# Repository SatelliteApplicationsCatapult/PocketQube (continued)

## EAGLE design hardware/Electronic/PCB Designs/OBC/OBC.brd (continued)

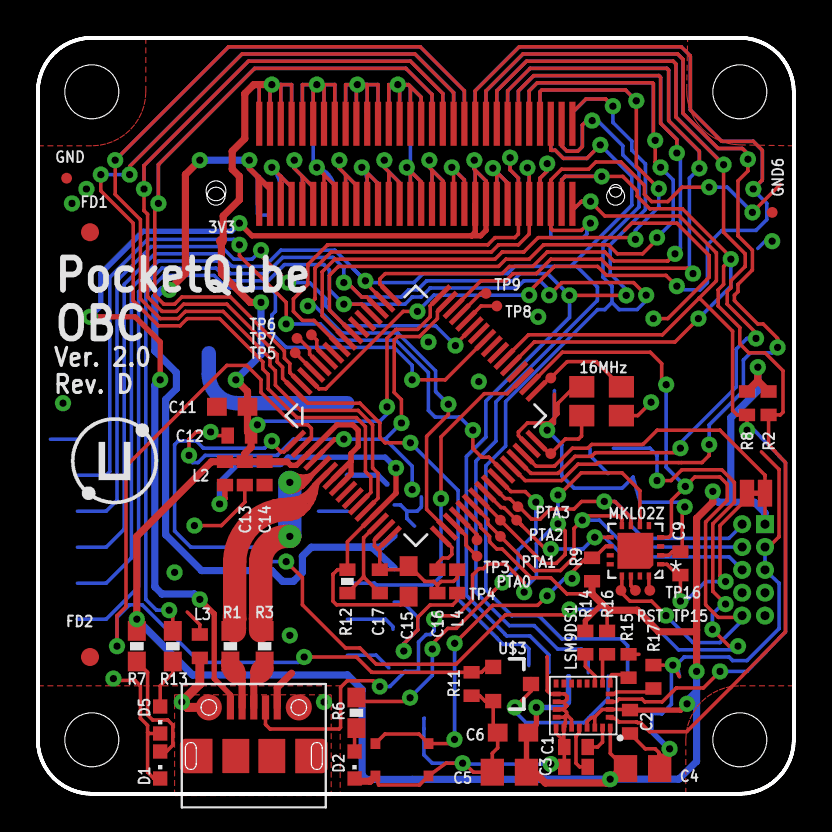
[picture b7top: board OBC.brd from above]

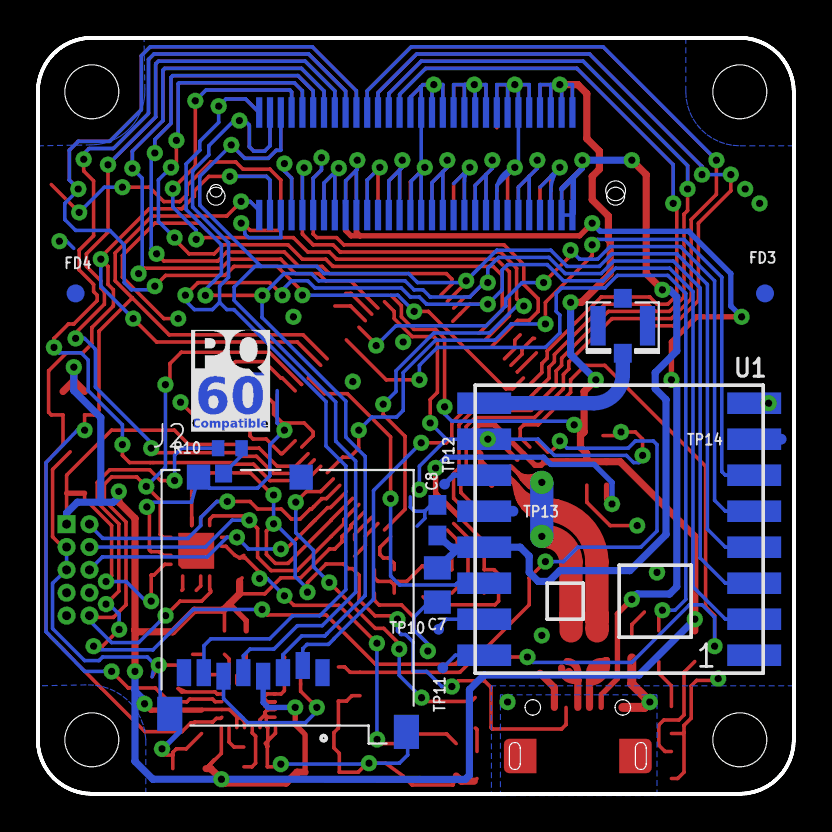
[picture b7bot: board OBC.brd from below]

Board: 2 copper layers, 42.0 x 42.0 mm, 82 parts (16 on the bottom side), 79 nets.

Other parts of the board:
U$2: PQ60_CMP
U$10: UBO_LOGO
U$13: SA_LOGO_SMALL

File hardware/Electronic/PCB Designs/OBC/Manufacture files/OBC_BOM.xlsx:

Parts | Manufacturer | Part number | Value | Qty | Package | Description | Distributor | Order code | Notes | ROHS | Temp range
3V3, GND, GND6, PTA0, PTA1, PTA2, PTA3, RST, TP1, TP2, TP3, TP4, TP5, TP6, TP7,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 |  | PTR1TP06R |  | 24 | TP06R | TEST PIN |  |  | Do not populate
C1, C2, C9, C12, C13, C14, C16, C17 |  | C-EUC0402 | 0.1uF | 8 | C0402 | CAPACITOR, European symbol |  |  | Any compatible X7R MLCC
C11, C15 |  | C-EUC0603 | 2.2uF | 2 | C0603 | CAPACITOR, European symbol |  |  | Any compatible X7R MLCC
C3 |  | C-EUC0402 | 10nF | 1 | C0402 | CAPACITOR, European symbol |  |  | Any compatible X7R MLCC
C4, C5, C7 |  | C-EUC0805 | 10uF | 3 | C0805 | CAPACITOR, European symbol |  |  | Any compatible X7R MLCC
C6, C8 |  | C-EUC0603 | 1uF | 2 | C0603 | CAPACITOR, European symbol |  |  | Any compatible X7R MLCC
D1 | Kingbright | KPT-1608EC | Red | 1 | CHIPLED_0603 | LED | Farnell | 2099221RL | Or any compatible 0603 SMD low power red LED | Yes | -40 to 85
D2 | Kingbright | KPG-1608QBC-D | Blue | 1 | CHIPLED_0603 | LED | Farnell | 1686063RL | Or any compatible 0603 SMD low power blue LED | Yes | -40 to 85
D5 | Kingbright | KPTD-1608SYCK | Yellow | 1 | CHIPLED_0603 | LED | Farnell | 2449898 | Or any compatible 0603 SMD low power yellow LED | Yes | -40 to 85
ERASE | Panasonic | EVPAF7B70 |  | 1 | EVPAF7B70 | Tactile switch | Farnell | 2425605 | Alternative suppliers available | Yes | -40 to 85
FD1, FD2, FD3, FD4 |  | FIDUCIAL |  | 4 | FIDUCIAL_1MM | For use by pick and place machines to calibrate the vision/machine, 1mm |  |  | Do not populate
J2 | Molex | 47352-1001 |  | 1 | MOLEX_47352-1001 | 1.10mm Pitch microSD Card Connector, Push-Push Type, with VSS (Supply Voltage G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 | RS Components | 720-6016P | Alternative suppliers available | Yes | -20 to 85
L2, L3, L4 | Murata | BLM15HG601SN1 |  | 3 | 402 | EMIFIL (R) Chip Ferrite Bead for GHz Noise | RS Components | 724-1289P | Alternative suppliers available | Yes | -55 to 125
LSM9DS1 | STMicroelectronics | LSM9DS1TR |  | 1 | LGA24-8X4 | LSM9DS1 3D accelerometer, gyroscope & magnetometer | Mouser | 511-LSM9DS1TR | Alternative suppliers available | Yes | -40 to 85
NDK_NX3225SA | Epson | X1E0000210117 TSX-3225 16MHZ 9PF | 16MHz | 1 | 4SMD_DFN_LCC | 16 MHz SMD crystal | Farnell | 2471850 | Must be 16 MHz, 9 pF, ≤10ppm, 3.2x2.5 crystal | Yes | -20 to 75
PQ60_HEADER | Hirose | FX8C-60P-SV6(91) |  | 1 | FX8C-060P-SV4(92) | Header | Mouser | 798-FX8C60PSV691 | Alternative suppliers available, however ensure the FX8C60PSV6 part is used, no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 | Yes
PQ60_RECEPTACLE |  | FX8C-060S-SV(92) |  | 1 | FX8C-060S-SV(92) |  |  |  | Do not populate | Yes
R1, R3 |  | RESISTOR0603-RES | 33R | 2 | 0603-RES | Resistor |  |  | Any standard chip SMD resistor, 1% tolerance or better
R12 |  | RESISTOR0402-RES | 10K | 1 | 0402-RES | Resistor |  |  | Any standard chip SMD resistor, 1% tolerance or better
R14, R15, R16, R17 |  | R-EU_R0402 | 10K | 4 | R0402 | RESISTOR, European symbol |  |  | Any standard chip SMD resistor, 1% tolerance or better
R2, R8 |  | R-EU_R0402 | 4.7K | 2 | R0402 | RESISTOR, European symbol |  |  | Any standard chip SMD resistor, 1% tolerance or better
R6, R7, R13 |  | RESISTOR0603-RES | 330R | 3 | 0603-RES | Resistor |  |  | Any standard chip SMD resistor, 1% tolerance or better
R9, R10, R11 |  | R-EU_R0402 | 22K | 3 | R0402 | RESISTOR, European symbol |  |  | Any standard chip SMD resistor, 1% tolerance or better
SJ3 |  | SJNC |  | 1 | SJNC | Solder jumper |  |  | Do not populate
U$1 | NXP | MKL02Z32VFG4SMD |  | 1 | QFN16 | Kinetis KL02 32 KB Flash |  |  | This must be pre-programmed with Teensy bootloader. We will supply this compone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
U$11 | Molex | 105017-0001 |  | 1 | USB-MICRO-TABS | Micro USB type B connector | Farnell | 2293836 | Alternative suppliers available | Yes | -30 to 85
U$3 | Nexperia | PMV40UN2R |  | 1 | SOT23-3 | N-channel trench MOSFET | Mouser | 771-PMV40UN2R | Alternative suppliers available | Yes | -55 to 150
U$4 | NXP | MK20DX256VLH7 |  | 1 | QFP50P1200X1200X160-64N | This is a footprint for the MK20dx256VHL7, the chip at the heart of the Teensy 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 | Farnell | 2133577 | Alternative suppliers available. | Yes | -40 to 105
U$9 |  | SWD_10_PIN |  | 1 | SWD_10_PIN |  |  |  | Do not populate
U.FL | Hirose | U.FL-R-SMT-1(10) |  | 1 | U.FL | SMD antenna connector- WRL-09144 | Farnell | 1688077 | Alternative suppliers available | Yes | -40 to 90
U1 | SparkFun | COM-13910 |  | 1 | RFM69HCW-XXXS2 | Wireless transceiver | Mouser | 474-COM-13910 | Alternative suppliers available but must be 433 MHz, HCW variant | Yes | -55 to 115
 |  |  |  | Partlist exported from C:/Users/Ken.Diep/repos/hardware/Electronic/PCB Designs/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

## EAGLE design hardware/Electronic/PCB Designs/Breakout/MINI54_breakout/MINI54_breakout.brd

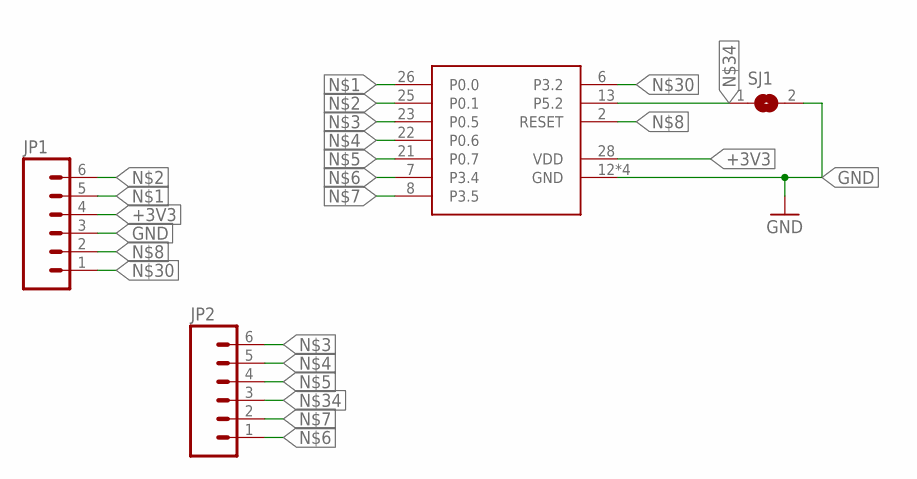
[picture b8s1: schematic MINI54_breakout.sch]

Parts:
JP1, JP2: M06LONGPADS; 1X06_LONGPADS
SJ1: SJ
U$9: MINITAN54-QFN; QFN50P500X500X100-33N

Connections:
+3V3: JP1.4, U$9.28 (VDD)
GND: JP1.3, SJ1.2, U$9.12 (GND), U$9.17 (GND), U$9.32 (GND), U$9.33 (GND)
unnamed: JP1.5, U$9.26 (P0.0)
unnamed: JP1.6, U$9.25 (P0.1)
unnamed: JP2.6, U$9.23 (P0.5)
unnamed: JP2.5, U$9.22 (P0.6)
unnamed: JP2.4, U$9.21 (P0.7)
unnamed: JP2.1, U$9.7 (P3.4)
unnamed: JP2.2, U$9.8 (P3.5)
unnamed: JP1.2, U$9.2 (RESET)
unnamed: JP1.1, U$9.6 (P3.2)
unnamed: JP2.3, SJ1.1, U$9.13 (P5.2)

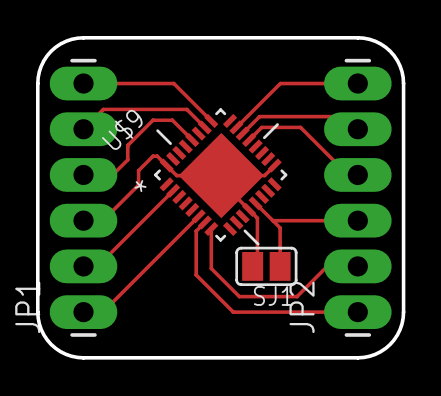
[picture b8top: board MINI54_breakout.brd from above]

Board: 2 copper layers, 20.3 x 17.8 mm, 4 parts (0 on the bottom side), 12 nets.
